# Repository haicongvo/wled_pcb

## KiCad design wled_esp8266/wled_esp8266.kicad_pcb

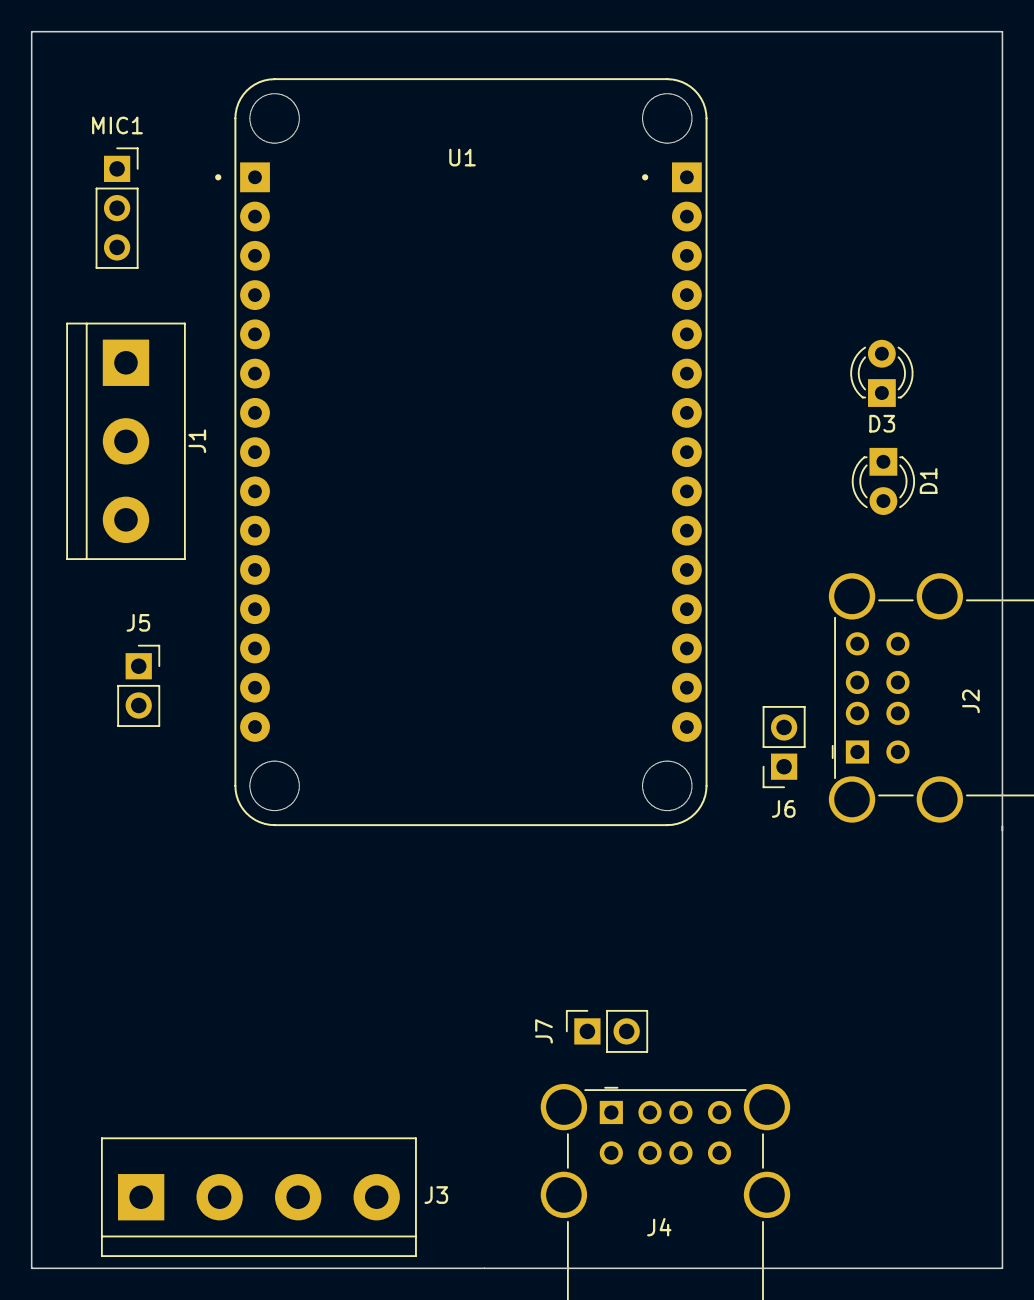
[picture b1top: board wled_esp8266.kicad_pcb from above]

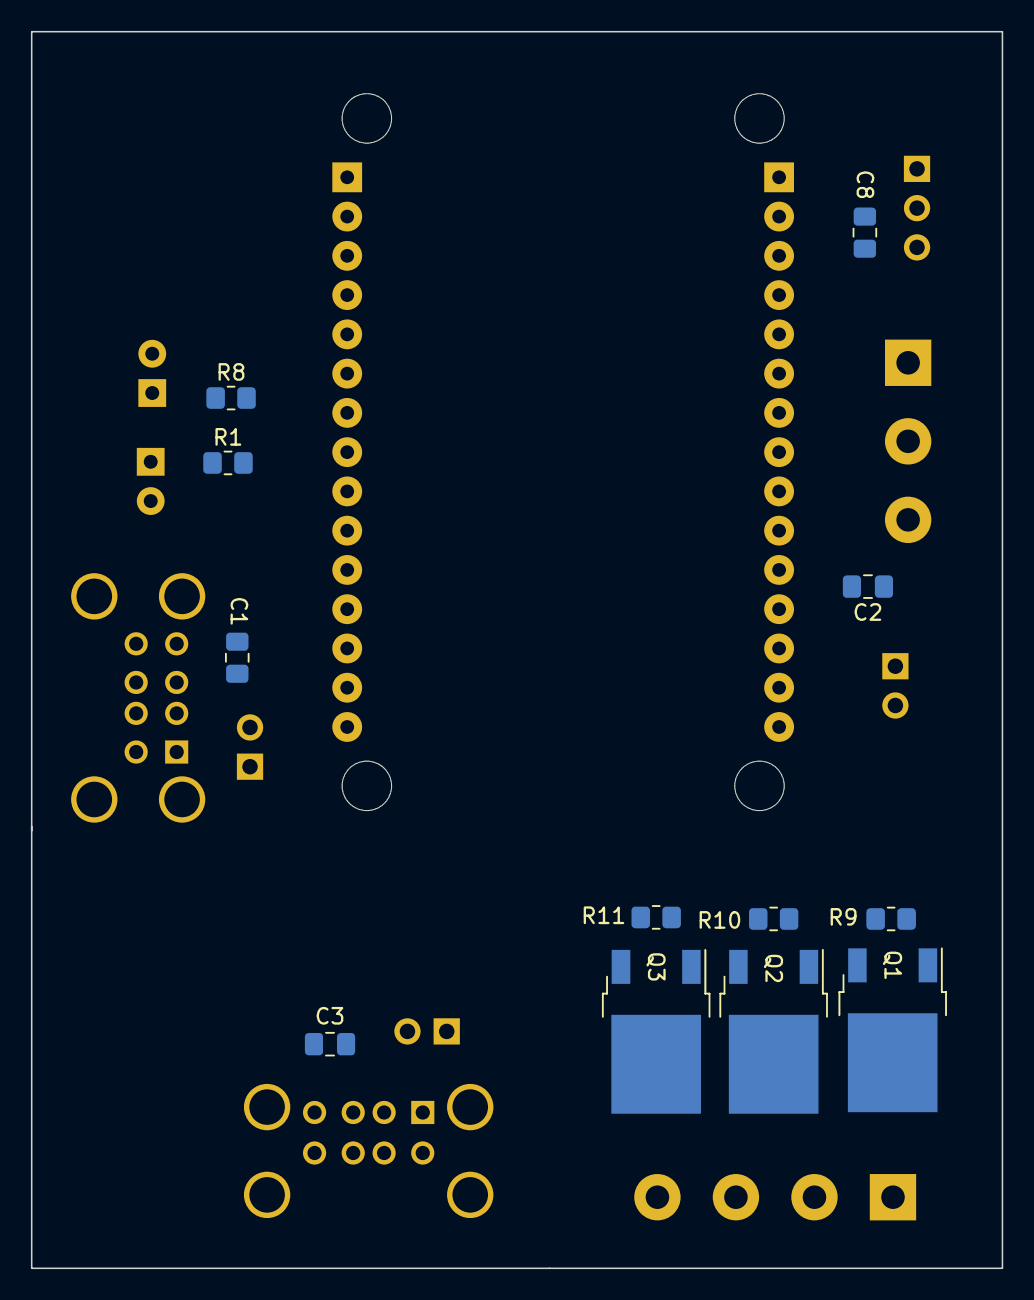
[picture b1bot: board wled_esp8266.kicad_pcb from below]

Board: 2 copper layers, 62.8 x 80.0 mm, 23 parts (12 on the bottom side), 16 nets, no tracks yet.

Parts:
C1, C2, C3, C8: 100nF; C_0805_2012Metric_Pad1.18x1.45mm_HandSolder
D1, D3: LED; LED_D3.0mm
J1: PWR; TerminalBlock_bornier-3_P5.08mm
J2, J4: USB_A_Stacked; USB_A_Wuerth_61400826021_Horizontal_Stacked
J3: Screw_Terminal_01x04; TerminalBlock_bornier-4_P5.08mm
J5, J6, J7: Conn_01x02; PinSocket_1x02_P2.54mm_Vertical
MIC1: Conn_01x03; PinSocket_1x03_P2.54mm_Vertical
Q1, Q2, Q3: IRF3708; TO-252-2
R1: 330; R_0805_2012Metric_Pad1.20x1.40mm_HandSolder
R8: 1K; R_0805_2012Metric_Pad1.20x1.40mm_HandSolder
R9, R10, R11: 10K; R_0805_2012Metric_Pad1.20x1.40mm_HandSolder
U1: ESP8266Nodemcu; LoLinNodeMcu(esp8266)

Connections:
+3V3: C8.1, MIC1.2, U1.5 (3V3)
+5V: D1.2 (A), J1.2, J5.2, J6.1, J7.1
+12V: C2.1, D3.2 (A), J1.3, J3.1
BLUE: J3.4, Q3.2 (D)
B_LED: Q3.1 (G), R11.1, U1.29 (D1)
GND: C1.2, C2.2, C3.2, C8.2, J1.1, J2.4 (GND1), J2.8 (GND2), J4.4 (GND1), J4.8 (GND2), MIC1.3, Q1.3 (S), Q2.3 (S), Q3.3 (S), R1.2, R8.2, R9.2, R10.2, R11.2, U1.2 (GND), U1.17 (GND)
GREEN: J3.3, Q2.2 (D)
G_LED: Q2.1 (G), R10.1, U1.23 (D5)
MICRO: MIC1.1, U1.15 (A0)
unnamed: C1.1, J2.1 (VBUS1), J2.5 (VBUS2), J6.2
unnamed: C3.1, J4.1 (VBUS1), J4.5 (VBUS2), J7.2
unnamed: D1.1 (K), R1.1
unnamed: D3.1 (K), R8.1
unnamed: J5.1, U1.1 (Vin)
RED: J3.2, Q1.2 (D)
R_LED: Q1.1 (G), R9.1, U1.28 (D2)

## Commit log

2022-11-21 updat
2022-11-21 update 2
2022-11-22 update pcb
2022-12-01 update new pcb
